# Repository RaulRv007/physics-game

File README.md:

# Physics-Based Multiplayer Platformer 🎮✨

## Overview

This repository contains a physics-driven, multiplayer platformer game built with **p5.js** and **Matter.js**, targeting the Grade 11/12 ICS2/3x Programming curriculum. Key features include:

* **Procedural Level Generation** 🏗️: Chunks of varying types (flat, stairs, pits, swings, climbable sections) are generated in sequence.
* **Tethered Multiplayer** 🤝: Up to 4 players are connected by ropes, introducing cooperative mechanics.
* **Digital Countdown Timer** ⏲️: A 2-minute timer governs each play session.
* **Accessibility Keyboard** ♿⌨️: A custom BLE keyboard built on an ESP32 with 5 pushbuttons for alternative controls. This keyboard allows people with reduced mobility in their hands to play the game easily.
* **Custom PCB** 🛠️: Designed in KiCad to host the ESP32 and buttons.

---

## Table of Contents

1. [Design & Planning](#design--planning) 📝
2. [Installation and Setup](#installation-and-setup) 💻
3. [Game Controls](#game-controls) 🎮
4. [Code Structure](#code-structure) 🗂️
5. [Pseudocode](#pseudocode) 🧩
6. [Hardware Accessibility](#hardware-accessibility) ♿
7. [KiCad PCB Design](#kicad-pcb-design) 🛠️
8. [Future Improvements](#future-improvements) 🚀
9. [References](#references) 📚

---

## Design & Planning

Before writing code, the following steps were completed:

1. **Sketches** ✏️: Hand-drawn layouts showing:

    * Main menu with player-selection buttons
    * In-game HUD (timer, stamina bars)
    * Chunk types and transition logic
    * Graphics theme
    * Sprites style

2. **Specifications**:

    * **Audience**: Teens and beginner programmers.
    * **Unique Selling Point**: Cooperative, rope-tethered movement with procedurally generated chunks.
    * **Start/End**: Game starts at main menu; ends when timer runs out or players reach the end-zone.
    * **Scoring**: How fast the team gets the stolen piece into the endzone 🏁
    * **Challenge**: Random chunk sequences that adapt difficulty.
3. **Pseudocode**: High-level representations of core algorithms (see section below).

---

## Installation and Setup 💻

1. Clone the repo:

    ```bash
    git clone https://github.com/username/physics-platformer.git
    cd physics-platformer
    ```
2. Serve with a local HTTP server (required for `p5.js` assets):

    ```bash
    npx http-server .
    ```
3. Open `http://localhost:8080` in your browser.
4. Make sure the `assets/` folder is alongside `index.html`.

---

## Game Controls 🎮

* **Keyboard (default)**:

  * Player 1: W (jump), Q (left), E (right)
  * Player 2: X (jump), Z (left), C (right)
  * Player 3: O (jump), I (left), P (right)
  * Player 4: N (jump), B (left), M (right)
* **ESP32 BLE Keyboard** (alternative accessibility): 5 buttons mapped to jump/left/right for one player via BLE HID. Ideally everybody would have a different keyboard, but for testing we only produced one

---

## Code Structure 🗂️

```
/src
├── mySketch.js      # Main p5.js sketch and game loop
├── Chunks.js         # Procedural chunk definitions
├── MapGenerator.js  # Sequencing and world creation
├── Player.js        # Player class: physics body, controls, stamina
├── Button.js        # HUD buttons
├── Piece.js         # class that controls the stolne piece
├── DigitalTimer.js  # Countdown timer logic
└── BLEControl.ino   # ESP32 BLE Keyboard firmware
/assets             # Sprites, sounds and fonts
```

### Key Classes

* **Chunk**: `#createBodies()` methods for each type (`flat`, `stairs-up/down`, `pit-platforms`, `swing`, `climb`, `end`).
* **MapGenerator**: Reads a sequence array and instantiates `Chunk` objects at `startX + n * chunkWidth`.
* **Player**: Encapsulates Matter.js body, controls, stamina, and rope tethering.
* **DigitalTimer**: Uses `millis()` to compute and display remaining time.

---

## Pseudocode 🧩

### Chunk Sequence Generation

```pseudo
function chunkSequence(numChunks):
     sequence = ['flat']
     for i in 1..numChunks:
          last = sequence.last()
          if last in ['flat', 'stairs-up', 'pit-platforms']:
                nextType = random(['climb','stairs-down','pit-platforms','swing'])
          else:
                nextType = random(['climb','stairs-up','pit-platforms','swing'])
          sequence.append(nextType)
     sequence.append('end')
     return sequence
```

### MapGenerator.generate()

```pseudo
currentX = startX
for each type in chunkSequence:
     hasStairs = (peekNext == 'stairs-down')
     chunk = new Chunk(type, currentX, startY, chunkWidth, hasStairs)
     chunk.addToWorld(world)
     chunks.push(chunk)
     currentX += chunkWidth
# add final end chunk
```

### Player.handleControls()

```pseudo
controls = {id: {up,key, left,key, right,key}, ...}
for each player:
     if keyIsDown(controls[id].up) and stamina>=min:
          applyForce(0, jumpForce)
          reduceStamina()
     if keyIsDown(left): applyForce(-force,0)
     if keyIsDown(right): applyForce(force,0)
```

### DigitalTimer

```pseudo
elapsed = (millis() - startTime)/1000
remaining = max(0, totalSeconds - elapsed)
minutes = floor(remaining/60)
seconds = remaining % 60
if remaining==0: finished = true; onFinishCallback()
```

---

## Hardware Accessibility ♿

To support players with limited mobility, a custom BLE keyboard was designed:

* OnShape Assembly: [https://cad.onshape.com/documents/988dd76aecb75962d265d2b5/w/65d7c2b6c940bfe08a743b60/e/20221e8a806b94a1ca8db9d0?renderMode=0&uiState=683498fb14300841d7131ac3](https://cad.onshape.com/documents/988dd76aecb75962d265d2b5/w/65d7c2b6c940bfe08a743b60/e/20221e8a806b94a1ca8db9d0?renderMode=0&uiState=683498fb14300841d7131ac3)

1. **ESP32** configured as a BLE HID device using `BleKeyboard.h`.
2. **Pushbuttons**: 5 buttons wired to GPIO pins (Jump, Left, Right, Jump-Right, Jump-Left).
3. **Debounce Logic**: Simple software debounce with state flags and 10 ms delay.
4. **Firmware**: `assistive_button.ino` maps button presses to HID key codes (`W`, `Q`, `E`, etc.).

Plug in the ESP32 and pair it with your computer/game device. Buttons emulate a keyboard—no extra drivers needed.

The decision for this setup is that in total it would be really cheap to produce. and it has a high reproducibility. It is not the best design by far, the push buttons are too small that the user gets almost not haptic feedback when the button is pressed. However talking with the group, this was the easiest and cheapest solution that we came out with. Also as it uses a 3D printed cage, everybody can recreate it easily at home.

---

## KiCad PCB Design 🛠️

A custom PCB hosts the ESP32 module and buttons:

* **Schematic**: ESP32-WROOM module, 5 momentary pushbuttons, pull-up resistors, USB power.
* **Board Layout**: Compact footprint with labeled button silkscreen.
* **Gerbers**: Uploaded in `/pcb/gerbers/`.

---

## Future Improvements 🚀

* Custom chunk creation with a system similar to mario maker
* More chunks to increase game dynamic
* Once in the market, get the feedback from the players and tune the physics engine (Matter.js)
* Improve some problems on the design of the accesibility keyboard (It works but there are some problems on the design)

---

## References 📚

* Matter.js Documentation: [https://brm.io/matter-js/](https://brm.io/matter-js/)
* p5.js Reference: [https://p5js.org/reference/](https://p5js.org/reference/)
* KiCad EDA: [https://kicad.org/](https://kicad.org/)
* ESP32 BLE HID: `BleKeyboard` library examples

---

*Good luck and have fun playing! 🎉*

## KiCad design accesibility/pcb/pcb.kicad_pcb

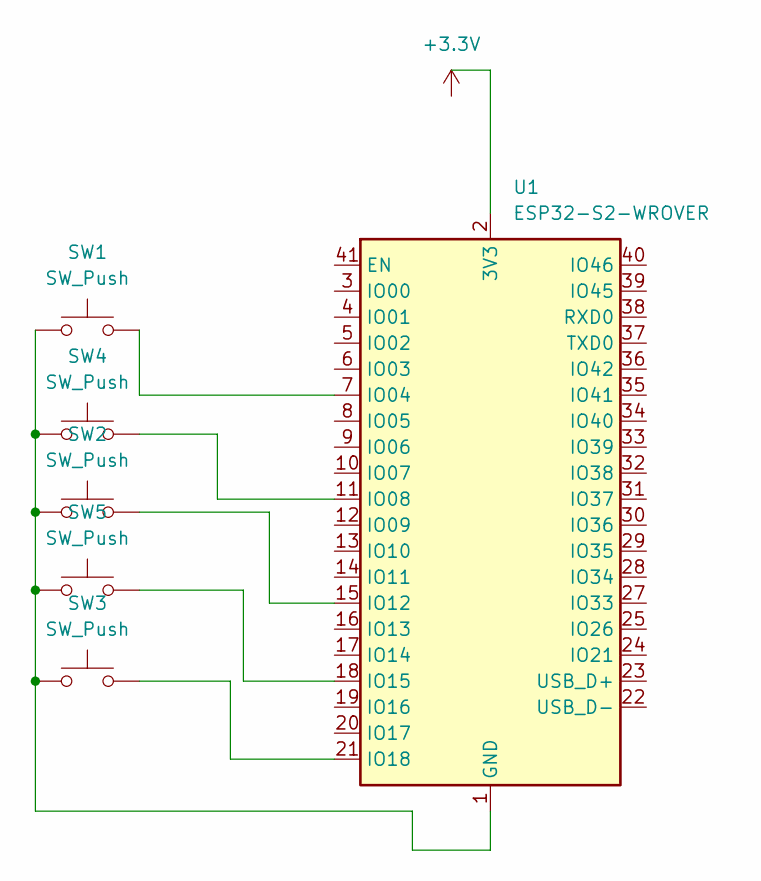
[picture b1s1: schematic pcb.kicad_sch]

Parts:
SW1, SW2, SW3, SW4, SW5: SW_Push; SW_SPST_PTS645
U1: ESP32-S2-WROVER

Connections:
unnamed: SW1.1, SW2.1, SW3.1, SW4.1, SW5.1, U1.1 (GND), U1.26 (GND), U1.42 (GND), U1.43 (GND)
unnamed: SW1.2, U1.7 (IO04)
unnamed: SW4.2, U1.11 (IO08)
unnamed: SW2.2, U1.15 (IO12)
unnamed: SW5.2, U1.18 (IO15)
unnamed: SW3.2, U1.21 (IO18)

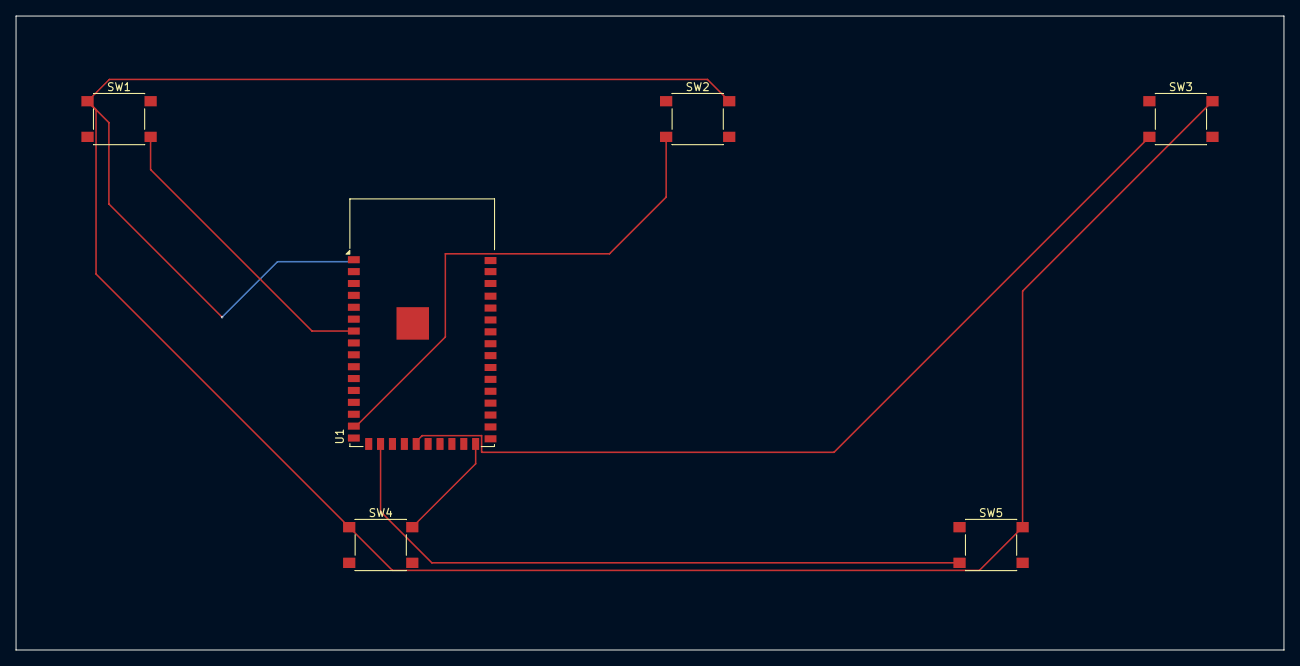
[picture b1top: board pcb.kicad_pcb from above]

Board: 2 copper layers, 160.0 x 80.0 mm, 6 parts (0 on the bottom side), 6 nets.

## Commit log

2025-05-17 added basic functionality, movement of players exists, physics engine works, everything is in their respective clases so its easier to reproduce
2025-05-17 added possibility to add a constraint to the piece to steal
2025-05-17 added camera following
2025-05-20 finished chunk system with some chunk examples, to talk with gorup
2025-05-20 added accesibility 3d models (prototype)
2025-05-20 added climbing chunk
2025-05-21 winning system works
2025-05-23 added jump stamina and added button to come back when the game is finished
2025-05-23 added most of the graphics and player selection
2025-05-23 added timer
2025-05-25 added README
2025-05-25 added some emojis to the README to make it more fun
2025-05-26 added sound and high score system. THERE IS A FEATURE IN THE PROWSERS CALLED LOACALSTORAGE!!!! it makes everything way easier
2025-05-26 demo
2025-05-26 added instructions
